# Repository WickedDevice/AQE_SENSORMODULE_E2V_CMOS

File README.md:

AQE_SENSORMODULE_E2V_CMOS
=========================

EAGLE6 CAD files for the e2v MICS sensors

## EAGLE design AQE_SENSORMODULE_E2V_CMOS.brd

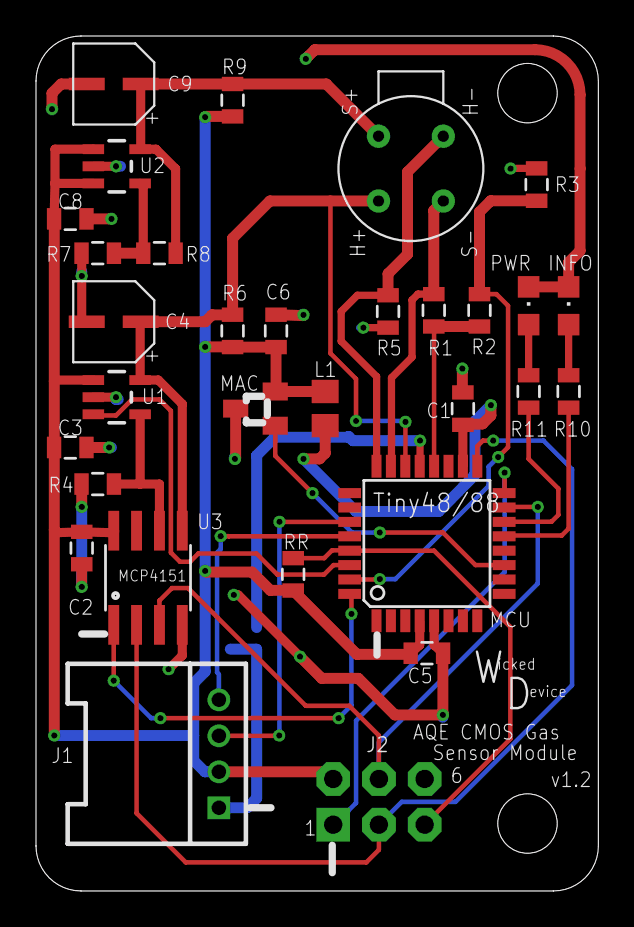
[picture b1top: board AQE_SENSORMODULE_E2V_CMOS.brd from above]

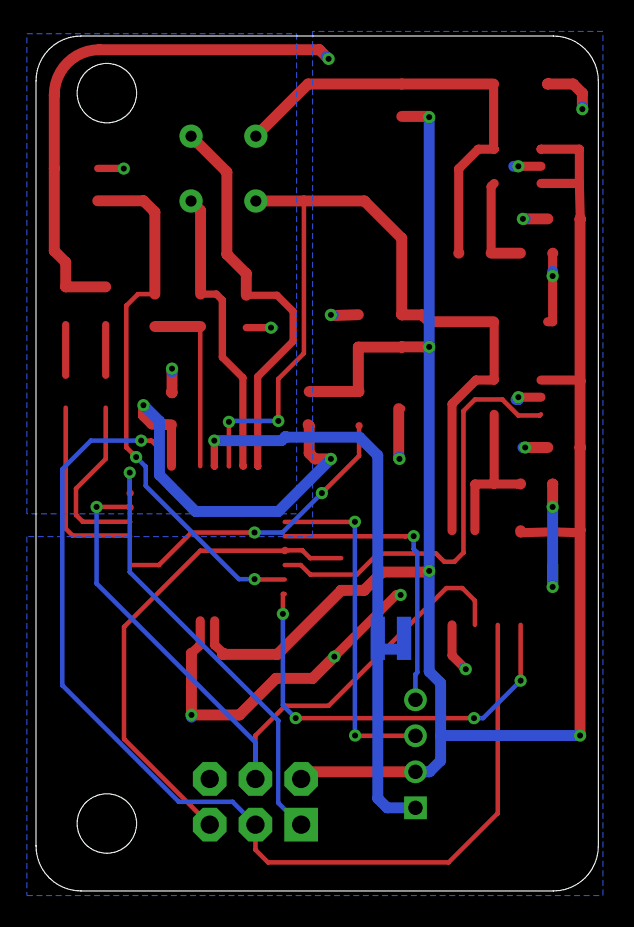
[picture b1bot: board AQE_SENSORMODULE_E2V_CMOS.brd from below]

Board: 2 copper layers, 31.2 x 47.5 mm, 35 parts (2 on the bottom side), 26 nets.

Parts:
C1, C2, C3, C5, C6, C8: 0.1uF; 0805
C4, C9: 10uF; TYPE-B_ALUMINUM_CAN
GAS: E2V; SR-4
INFO: GREEN; CHIPLED_0805
J1: 440055-4; 2.0_1X4_90
J2: AVR_SPI_PRG_6NS; 2X3-NS
JP1, JP2: STAND-OFF
L1: FERRITE; RCL_R0805
MAC: 11AA02E48; SOT23
MCU: ATTINY4832A; TQFP32-08
PWR: RED; CHIPLED_0805
R1, R2, R3: 0805
R4, R7: 2.4MOhm; 0805
R5: 10R; 0805
R6, R9: 0Ohm; 0805
R8: 2.2MOhm; 0805
R10, R11: 270ohm; 0805
RR: 10 kOhm; 0805
U1, U2: V_REG_LDOSMD; SOT23-5
U3: MCP41XXX; SO08
U$2, U$3: PLANE_COUPLER

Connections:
/POT_CS: MCU.32, U3.1
/R1_SEL: MCU.20, R1.1, R2.2
/R2_SEL: MCU.31, R2.1, R3.2
/RESET: J2.5, MCU.29, RR.1
AGND: C1.2, MCU.21, R3.1, R5.1, U$2.1
AVCC: C1.1, L1.1, MCU.18
GND: C2.2, C3.1, C4.P$2, C5.2, C6.2, C8.1, C9.P$2, INFO.C, J2.6, MAC.3, MCU.5, PWR.C, R4.1, R7.1, U1.2, U2.2, U3.4, U$3.1
HEATER_EN: MCU.30, U1.3
HEATER_FEEDBACK: GAS.FIGV+/E2V-, MCU.24, R5.2
HEATER_VCC: C4.P$1, GAS.FIGSIG/E2VH+, MCU.22, R6.2, U1.5, U3.5
MAC_IO: MAC.1, MCU.11
MISO: J2.1, MCU.16
MOSI: J2.4, MCU.15, U3.3
unnamed: R7.2, R8.1, U2.4
unnamed: PWR.A, R11.1
unnamed: INFO.A, R10.1
POWER: MCU.14, R11.2
RETURN_GND: J1.1, U$2.2, U$3.2
RH-: R4.2, U1.4, U3.6
SCK: J2.3, MCU.17, U3.2
SCL: J1.4, MCU.28
SDA: J1.3, MCU.27
SENSOR: GAS.FIGV+/E2VSIG, MCU.23, R1.2
SENSOR_VCC: C9.P$1, GAS.FIGG/E2VS+, R8.2, R9.2, U2.5
STATUS: MCU.13, R10.2
VCC: C2.1, C3.2, C5.1, C6.1, C8.2, J1.2, J2.2, L1.2, MAC.2, MCU.4, R6.1, R9.1, RR.2, U1.1, U2.1, U2.3, U3.8

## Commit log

2012-05-05 initial schematics
2012-05-05 initial layout
2012-05-06 added pdfs
2012-05-14 aded MAC chip, switched to lm317 adjustable regulator, and re-routed the board by hand
2012-05-16 added second voltage regulator circuit, modified sensor circuit to allow 'sliding-scale' ADC approach, added standoff holes
2012-05-28 minor changes in routing and component placement for improved decoupling, more representative values for resistors, and minor changes to silk screen
2012-05-28 adding solderpad support files
2012-05-28 updated pictures
2012-06-03 last changes before switching heater approach to feedback controlled and changing microcontroller
2012-06-04 making progress on updates to incorporate heater feedback control
2012-06-04 routed additional signals, would like to separate analog ground plane
2012-06-06 incorporated changes for separating analog and digital gnd with a star topology. added possibility to shut off heater power, and added power filtering for analog vcc to mcu
2012-06-06 updated images
2012-06-06 updated board image with polygon fills filled
2012-06-14 incorporated several changes based on review comments
2012-06-15 updated schematic and board to make attiny48 pinout compatible with egg shield
2012-06-15 cosmetic update to make AGND an xref in the schematic
2012-09-10 updated files
2012-09-10 flipped J1 connector pinout around by 180 degrees

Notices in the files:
parts and their libraries:
SparkFun: Licensing: CC v3.0 Share-Alike You are welcome to use this library for commercial purposes.
